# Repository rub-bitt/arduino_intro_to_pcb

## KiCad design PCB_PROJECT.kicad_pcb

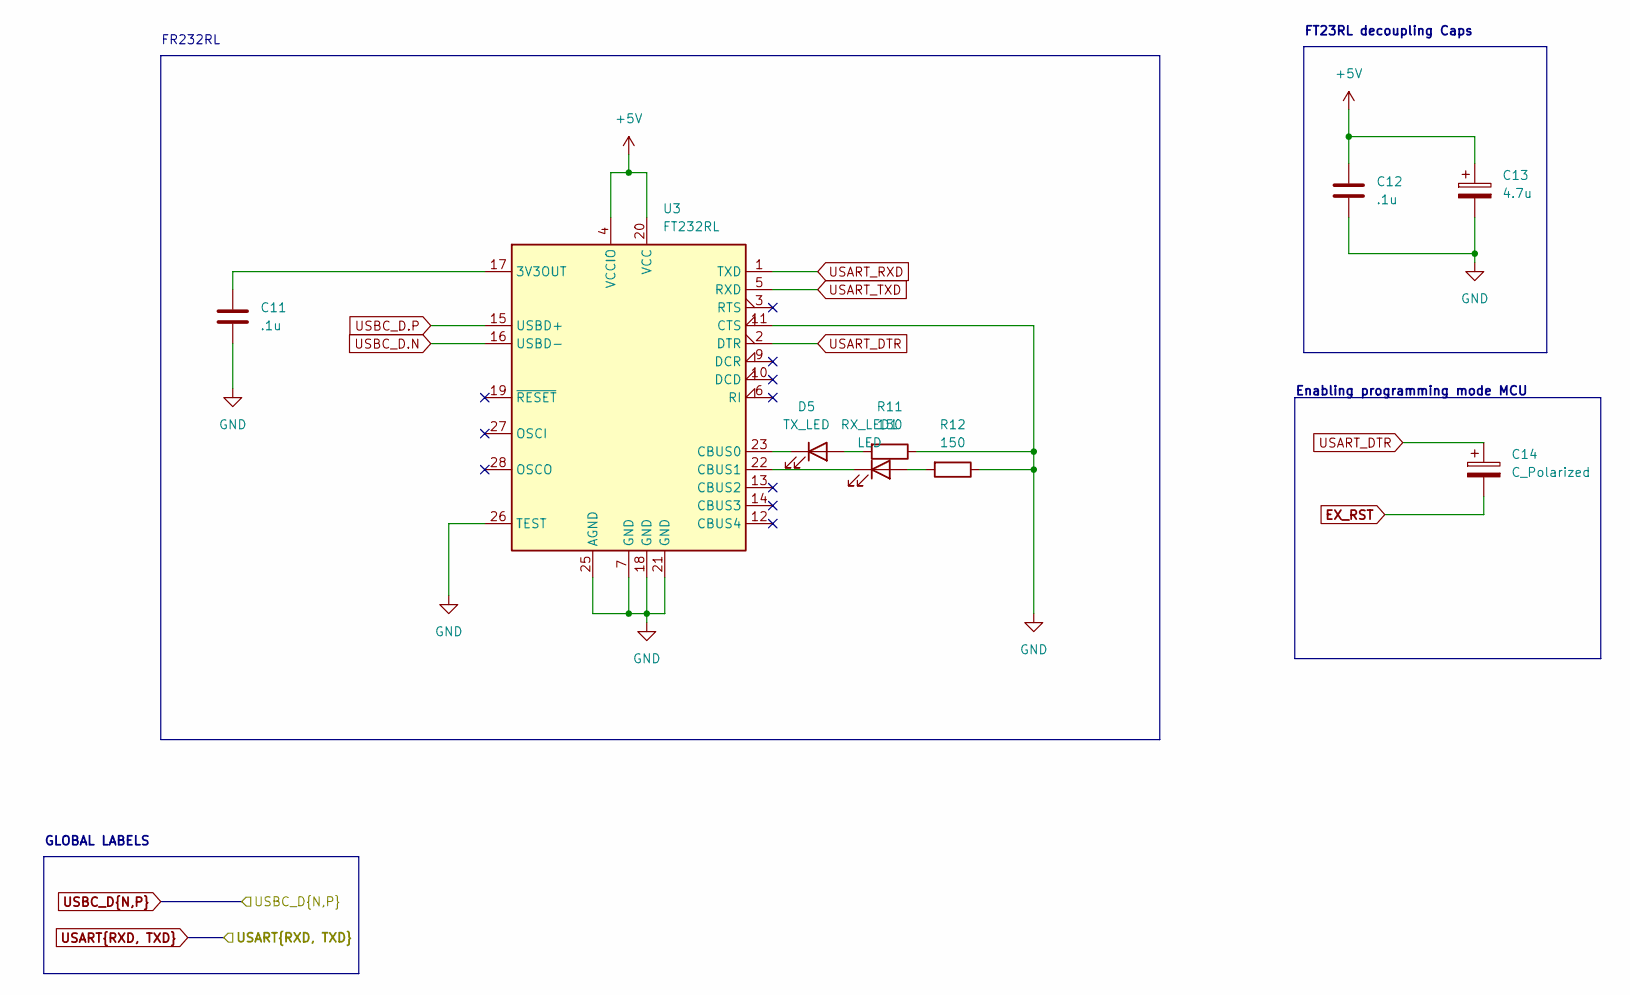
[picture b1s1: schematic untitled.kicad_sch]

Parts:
C11: .1u; C_0603_1608Metric
C12: .1u; C_0402_1005Metric
C13: 4.7u; C_0402_1005Metric
C14: C_Polarized; C_0603_1608Metric
D5: TX_LED; LED_0402_1005Metric
R11, R12: 150; R_0402_1005Metric
RX_LED1: LED; LED_0402_1005Metric
U3: FT232RL; SSOP-28_5.3x10.2mm_P0.65mm

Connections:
+5V: C12.1, C13.1, U3.4 (VCCIO), U3.20 (VCC); also elsewhere on the board
EX_RST: C14.2; also elsewhere on the board
GND: C11.2, C12.2, C13.2, R11.1, R12.1, U3.7 (GND), U3.11 (CTS), U3.18 (GND), U3.21 (GND), U3.25 (AGND), U3.26 (TEST); also elsewhere on the board
unnamed: D5.2 (A), R11.2
unnamed: D5.1 (K), U3.23 (CBUS0)
unnamed: R12.2, RX_LED1.2 (A)
unnamed: RX_LED1.1 (K), U3.22 (CBUS1)
unnamed: C11.1, U3.17 (3V3OUT)
USART_DTR: C14.1, U3.2 (DTR)
USART_RXD: U3.1 (TXD); also elsewhere on the board
USART_TXD: U3.5 (RXD); also elsewhere on the board
USBC_D.N: U3.16 (USBD-); also elsewhere on the board
USBC_D.P: U3.15 (USBD+); also elsewhere on the board

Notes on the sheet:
Enabling programming mode MCU
GLOBAL LABELS
FR232RL
FT23RL decoupling Caps

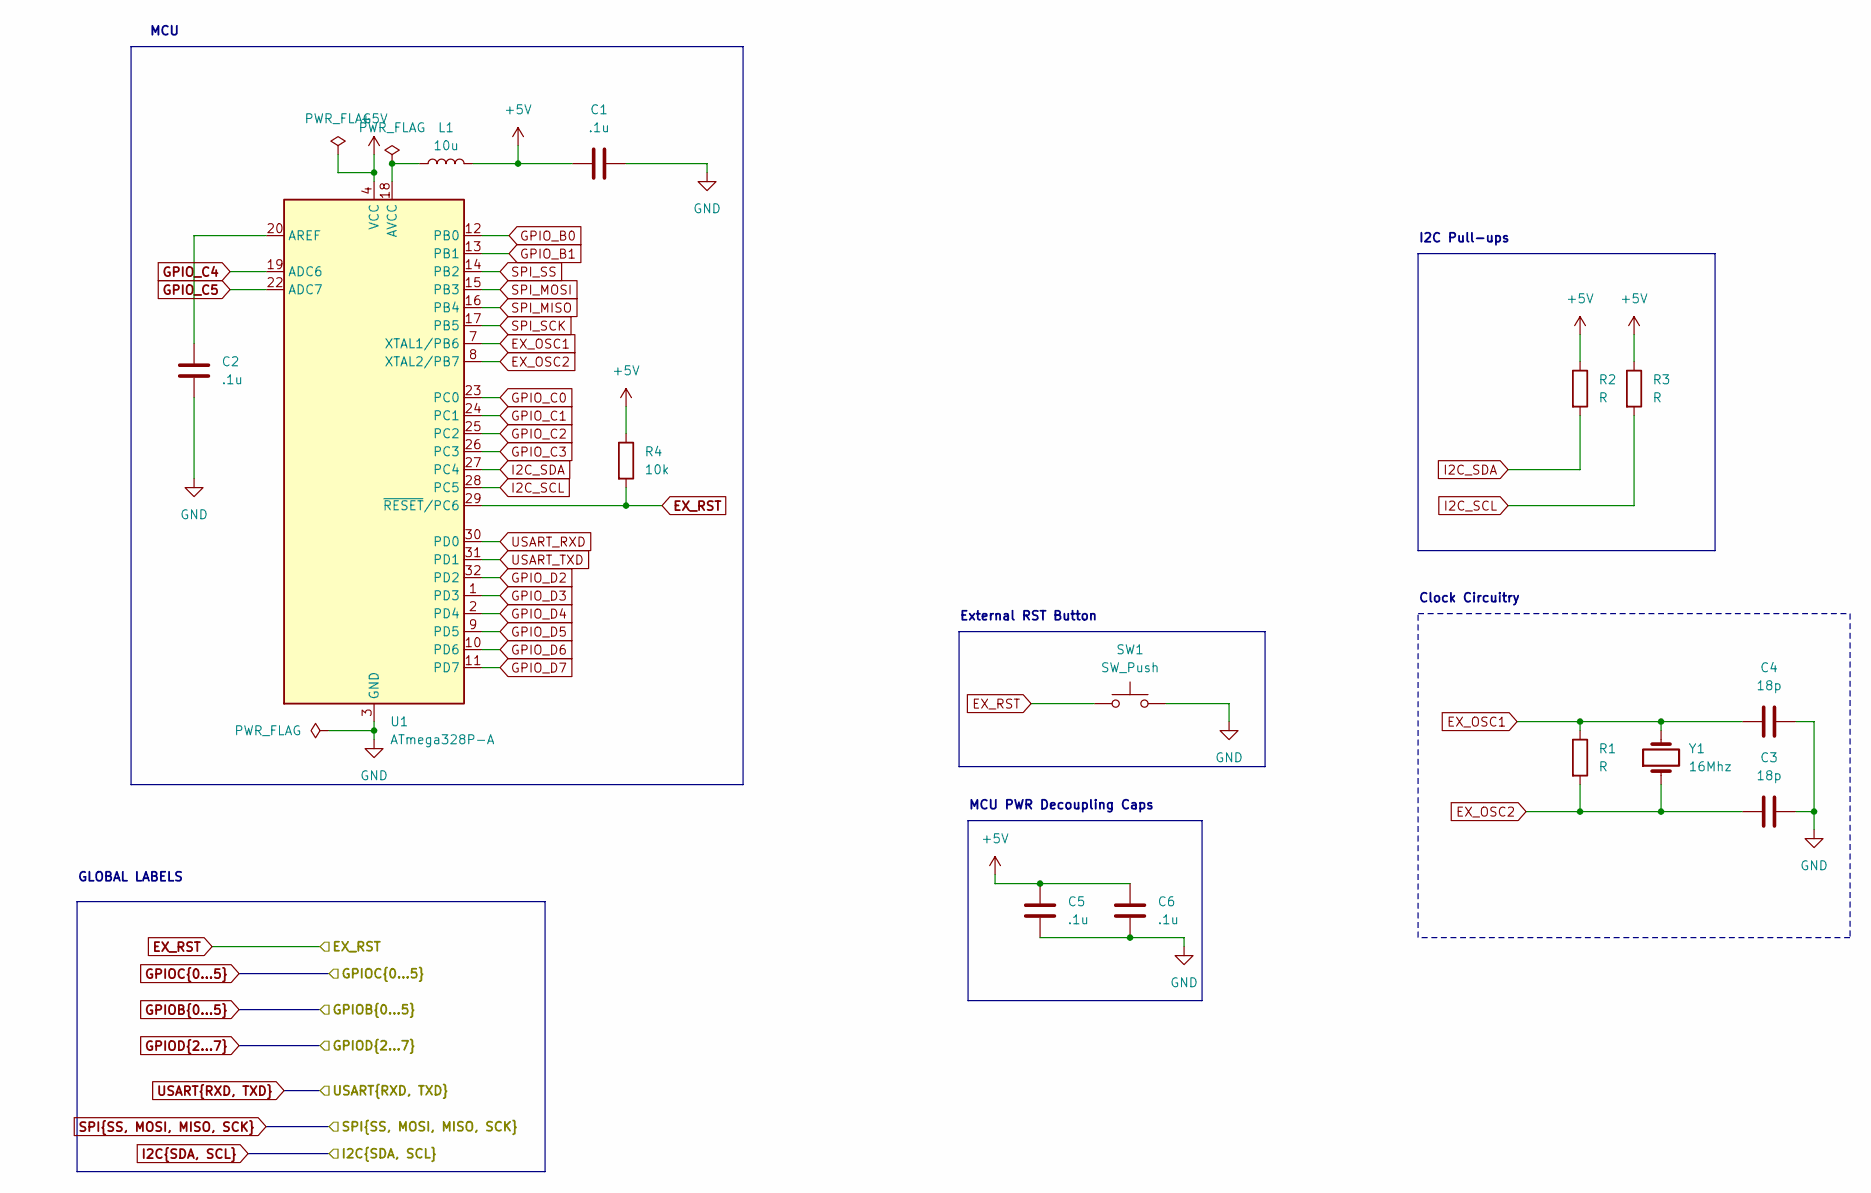
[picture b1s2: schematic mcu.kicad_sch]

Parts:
C1, C2, C5, C6: .1u; C_0402_1005Metric
C3, C4: 18p; C_0402_1005Metric
L1: 10u; L_0603_1608Metric
R1, R2, R3: R; R_0402_1005Metric
R4: 10k; R_0402_1005Metric
SW1: SW_Push; SW_Push_SPST_NO_Alps_SKRK
U1: ATmega328P-A; TQFP-32_7x7mm_P0.8mm
Y1: 16Mhz; Crystal_SMD_2012-2Pin_2.0x1.2mm

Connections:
+5V: C1.1, C5.1, C6.1, L1.2, R2.1, R3.1, R4.1, U1.4 (VCC), U1.6 (VCC); also elsewhere on the board
EX_OSC1: C4.1, R1.1, U1.7 (XTAL1/PB6), Y1.2
EX_OSC2: C3.1, R1.2, U1.8 (XTAL2/PB7), Y1.1
EX_RST: R4.2, SW1.1, U1.29 (~RESET/PC6); also elsewhere on the board
GND: C1.2, C2.2, C3.2, C4.2, C5.2, C6.2, SW1.2, U1.3 (GND), U1.5 (GND), U1.21 (GND); also elsewhere on the board
GPIO_B0: U1.12 (PB0); also elsewhere on the board
GPIO_B1: U1.13 (PB1); also elsewhere on the board
GPIO_C0: U1.23 (PC0); also elsewhere on the board
GPIO_C1: U1.24 (PC1); also elsewhere on the board
GPIO_C2: U1.25 (PC2); also elsewhere on the board
GPIO_C3: U1.26 (PC3); also elsewhere on the board
GPIO_C4: U1.19 (ADC6); also elsewhere on the board
GPIO_C5: U1.22 (ADC7); also elsewhere on the board
GPIO_D2: U1.32 (PD2); also elsewhere on the board
GPIO_D3: U1.1 (PD3); also elsewhere on the board
GPIO_D4: U1.2 (PD4); also elsewhere on the board
GPIO_D5: U1.9 (PD5); also elsewhere on the board
GPIO_D6: U1.10 (PD6); also elsewhere on the board
GPIO_D7: U1.11 (PD7); also elsewhere on the board
I2C_SCL: R3.2, U1.28 (PC5); also elsewhere on the board
I2C_SDA: R2.2, U1.27 (PC4); also elsewhere on the board
unnamed: C2.1, U1.20 (AREF)
unnamed: L1.1, U1.18 (AVCC)
SPI_MISO: U1.16 (PB4); also elsewhere on the board
SPI_MOSI: U1.15 (PB3); also elsewhere on the board
SPI_SCK: U1.17 (PB5); also elsewhere on the board
SPI_SS: U1.14 (PB2); also elsewhere on the board
USART_RXD: U1.30 (PD0); also elsewhere on the board
USART_TXD: U1.31 (PD1); also elsewhere on the board

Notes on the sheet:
MCU
MCU PWR Decoupling Caps
External RST Button
Clock Circuitry
I2C Pull-ups
GLOBAL LABELS

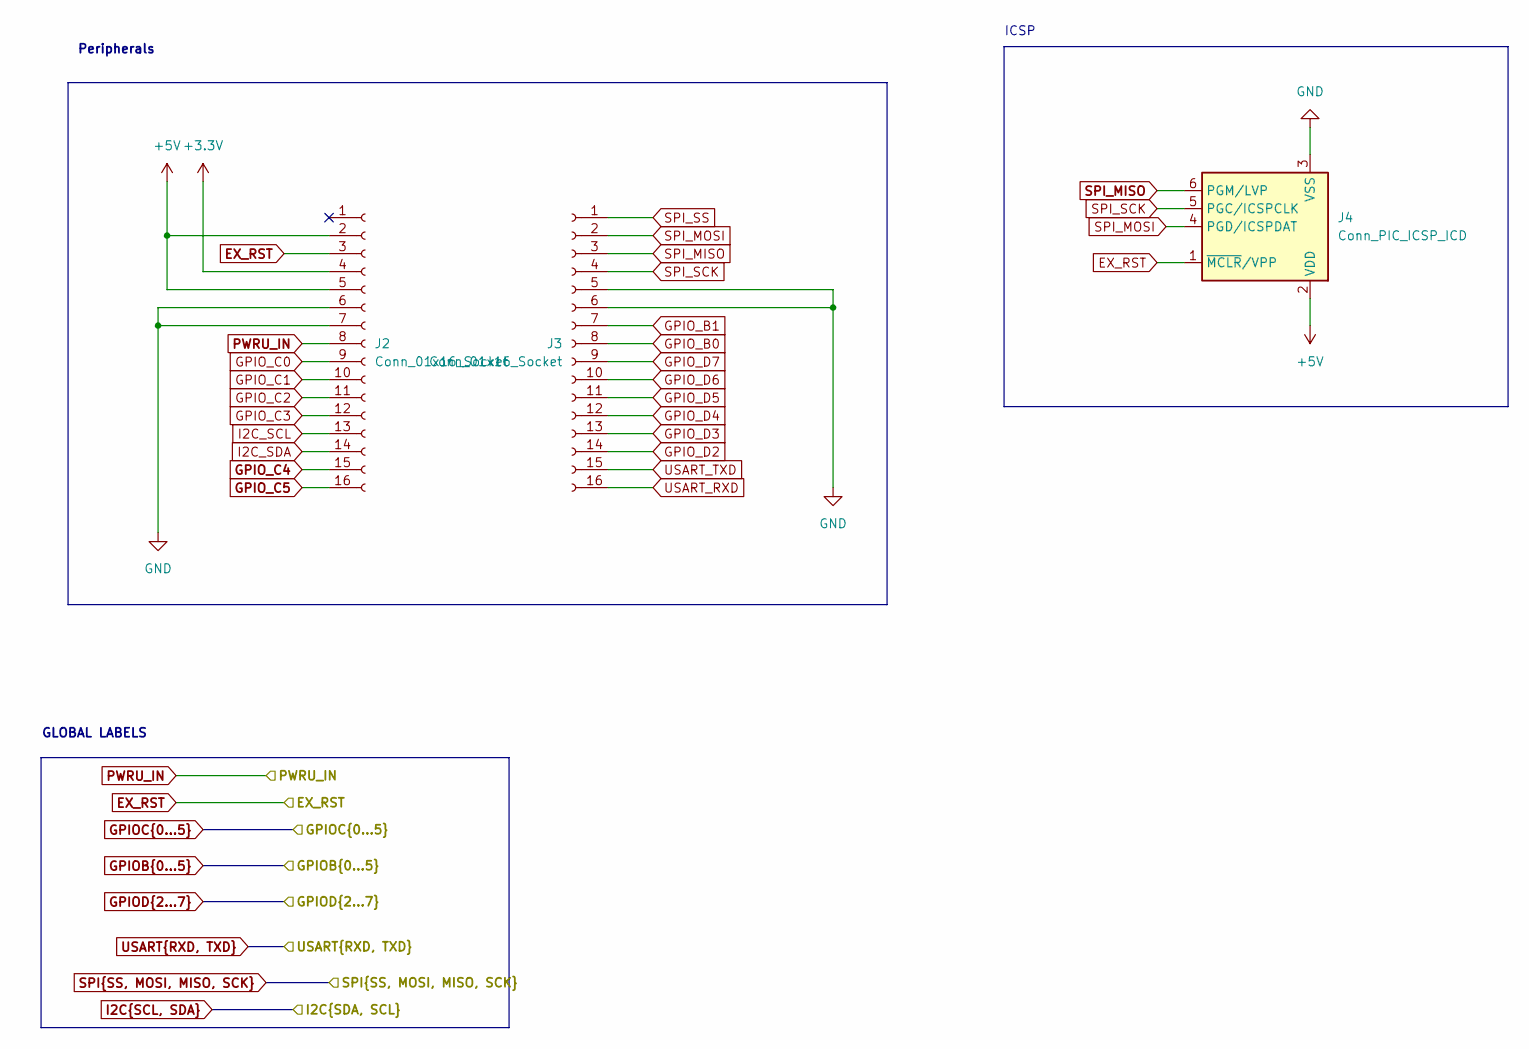
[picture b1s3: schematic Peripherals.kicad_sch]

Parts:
J2, J3: Conn_01x16_Socket; PinHeader_1x16_P2.54mm_Vertical
J4: Conn_PIC_ICSP_ICD; PinSocket_2x03_P2.54mm_Vertical

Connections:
+3.3V: J2.4; also elsewhere on the board
+5V: J2.2, J2.5, J4.2 (VDD); also elsewhere on the board
EX_RST: J2.3, J4.1 (~MCLR/VPP); also elsewhere on the board
GND: J2.6, J2.7, J3.5, J3.6, J4.3 (VSS); also elsewhere on the board
GPIO_B0: J3.8; also elsewhere on the board
GPIO_B1: J3.7; also elsewhere on the board
GPIO_C0: J2.9; also elsewhere on the board
GPIO_C1: J2.10; also elsewhere on the board
GPIO_C2: J2.11; also elsewhere on the board
GPIO_C3: J2.12; also elsewhere on the board
GPIO_C4: J2.15; also elsewhere on the board
GPIO_C5: J2.16; also elsewhere on the board
GPIO_D2: J3.14; also elsewhere on the board
GPIO_D3: J3.13; also elsewhere on the board
GPIO_D4: J3.12; also elsewhere on the board
GPIO_D5: J3.11; also elsewhere on the board
GPIO_D6: J3.10; also elsewhere on the board
GPIO_D7: J3.9; also elsewhere on the board
I2C_SCL: J2.13; also elsewhere on the board
I2C_SDA: J2.14; also elsewhere on the board
PWRU_IN: J2.8; also elsewhere on the board
SPI_MISO: J3.3, J4.6 (PGM/LVP); also elsewhere on the board
SPI_MOSI: J3.2, J4.4 (PGD/ICSPDAT); also elsewhere on the board
SPI_SCK: J3.4, J4.5 (PGC/ICSPCLK); also elsewhere on the board
SPI_SS: J3.1; also elsewhere on the board
USART_RXD: J3.16; also elsewhere on the board
USART_TXD: J3.15; also elsewhere on the board

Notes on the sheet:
ICSP
Peripherals
GLOBAL LABELS

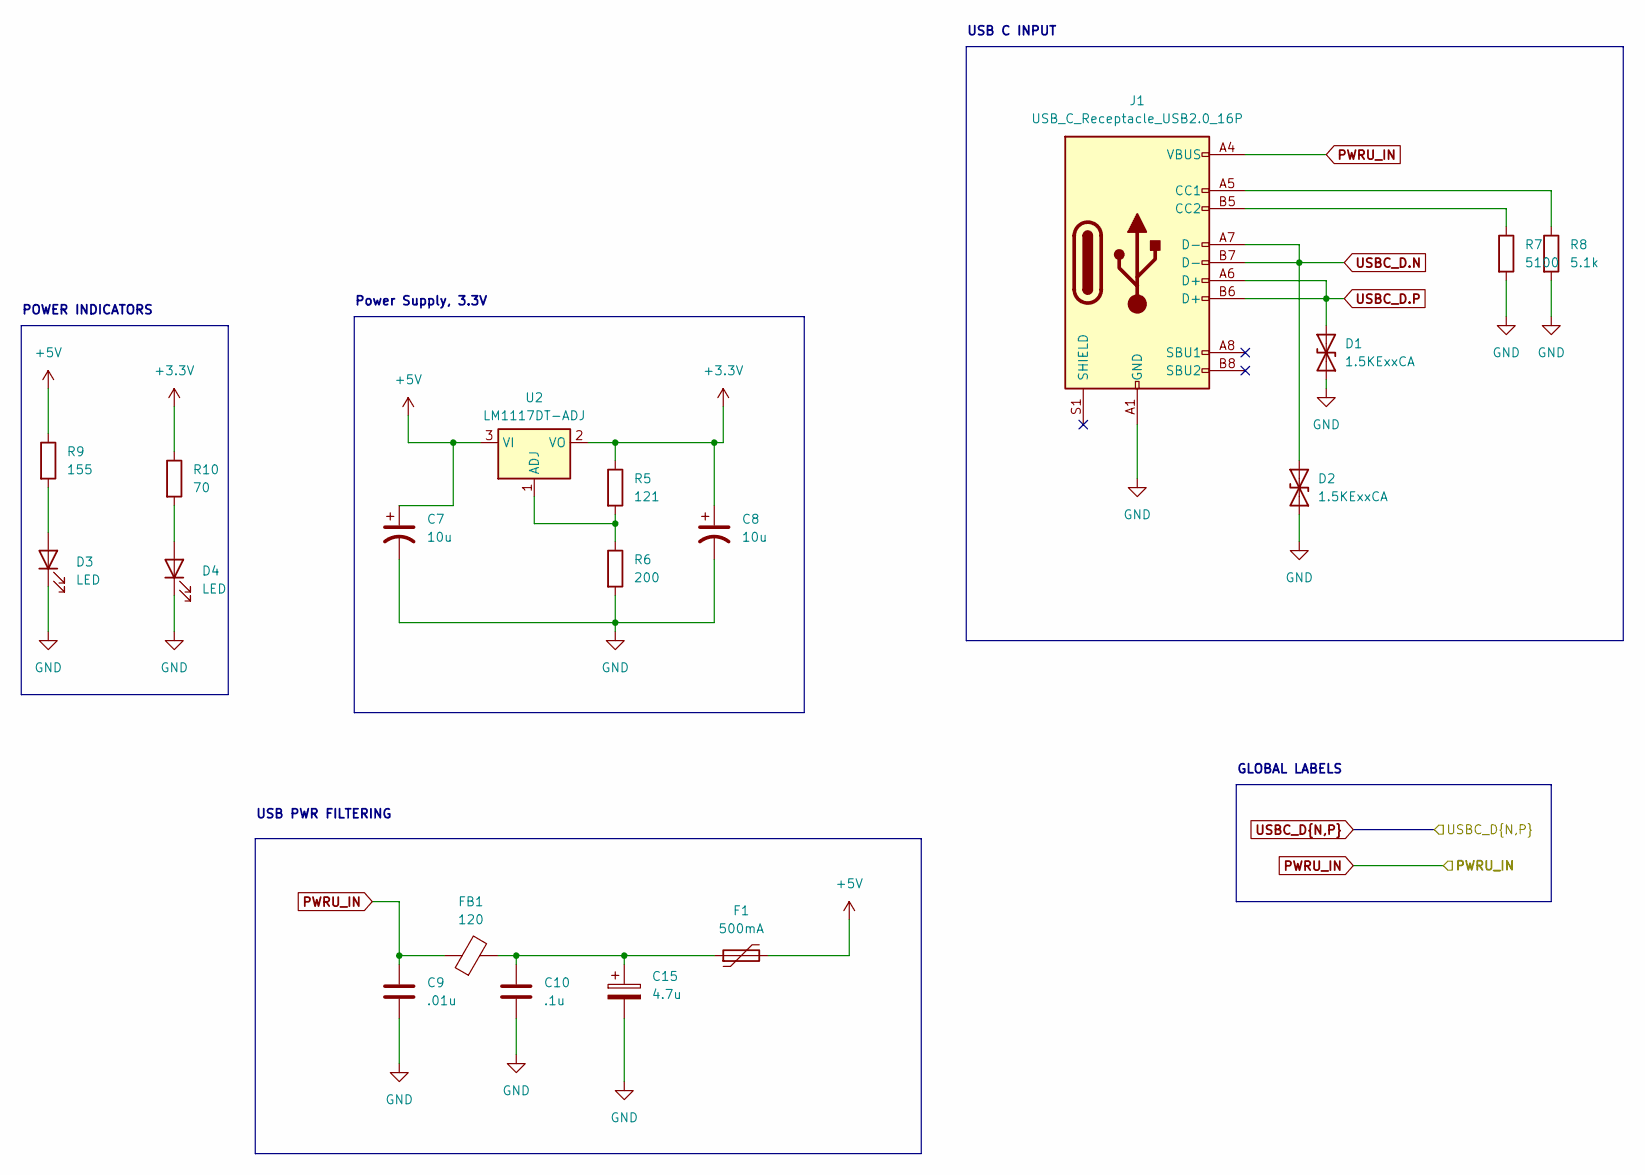
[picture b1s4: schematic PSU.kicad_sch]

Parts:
C7: 10u; C_0603_1608Metric
C8: 10u; C_0402_1005Metric
C9: .01u; C_0603_1608Metric
C10: .1u; C_0603_1608Metric
C15: 4.7u; C_0603_1608Metric
D1, D2: 1.5KExxCA; D_0201_0603Metric
D3, D4: LED; LED_0402_1005Metric
F1: 500mA; Fuse_1812_4532Metric
FB1: 120; R_0603_1608Metric
J1: USB_C_Receptacle_USB2.0_16P; USB_C_Receptacle_Palconn_UTC16-G
R5: 121; R_0402_1005Metric
R6: 200; R_0402_1005Metric
R7: 5100; R_0402_1005Metric
R8: 5.1k; R_0402_1005Metric
R9: 155; R_0402_1005Metric
R10: 70; R_0402_1005Metric
U2: LM1117DT-ADJ; SOT-223

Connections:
+3.3V: C8.1, R5.1, R10.1, U2.2 (VO); also elsewhere on the board
+5V: C7.1, F1.2, R9.1, U2.3 (VI); also elsewhere on the board
GND: C7.2, C8.2, C9.2, C10.2, C15.2, D1.1 (A1), D2.1 (A1), D3.1 (K), D4.1 (K), J1.A1 (GND), J1.A12 (GND), J1.B1 (GND), J1.B12 (GND), R6.2, R7.2, R8.2; also elsewhere on the board
unnamed: C10.1, C15.1, F1.1, FB1.2
unnamed: D3.2 (A), R9.2
unnamed: D4.2 (A), R10.2
unnamed: J1.A5 (CC1), R8.1
unnamed: J1.B5 (CC2), R7.1
unnamed: R5.2, R6.1, U2.1 (ADJ)
PWRU_IN: C9.1, FB1.1, J1.A4 (VBUS), J1.A9 (VBUS), J1.B4 (VBUS), J1.B9 (VBUS); also elsewhere on the board
USBC_D.N: D2.2 (A2), J1.A7 (D-), J1.B7 (D-); also elsewhere on the board
USBC_D.P: D1.2 (A2), J1.A6 (D+), J1.B6 (D+); also elsewhere on the board

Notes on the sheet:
GLOBAL LABELS
Power Supply, 3.3V
POWER INDICATORS
USB C INPUT
USB PWR FILTERING

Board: 2 copper layers, 45 parts (0 on the bottom side), 45 nets, no tracks yet.

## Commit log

2025-07-09 first pls
2025-07-09 placing
2025-07-09 placing updates
